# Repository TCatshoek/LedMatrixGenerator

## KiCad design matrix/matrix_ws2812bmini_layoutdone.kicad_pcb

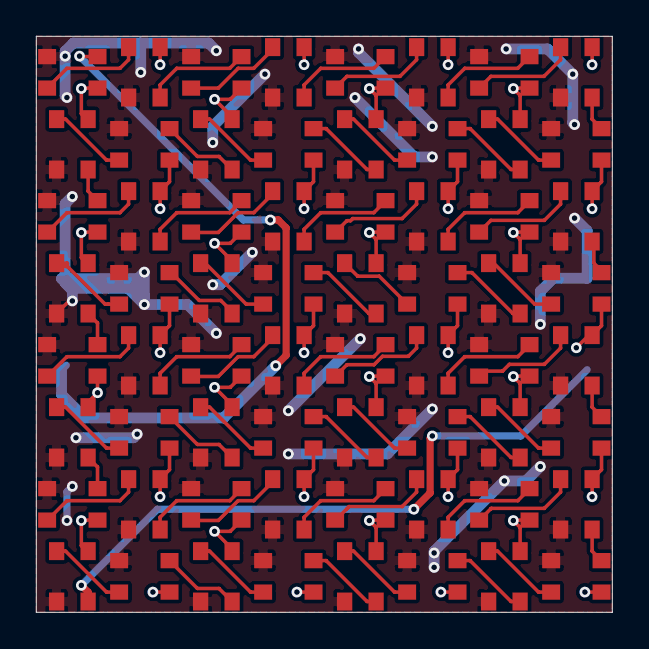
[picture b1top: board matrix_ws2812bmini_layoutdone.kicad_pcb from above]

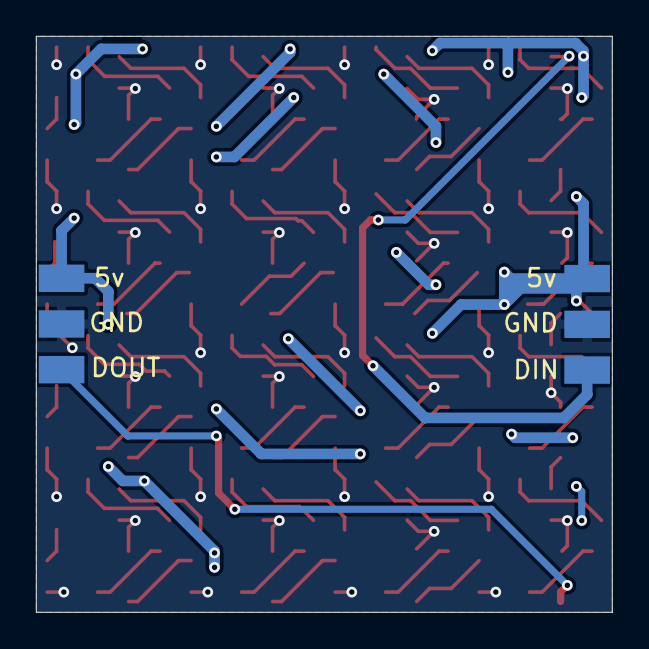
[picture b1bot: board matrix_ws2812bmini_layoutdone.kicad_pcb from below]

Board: 2 copper layers, 32.0 x 32.0 mm, 66 parts (2 on the bottom side), 67 nets.

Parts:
D1, D2, D3, D4, D5, D6, D7, D8, D9, D10, D11, D12, D13, D14, D15, D16, D17, D18, D19, D20, D21, D22, D23, D24, D25, D26, D27, D28, D29, D30, D31, D32, D33, D34, D35, D36, D37, D38, D39, D40, D41, D42, D43, D44, D45, D46, D47, D48, D49, D50, D51, D52, D53, D54, D55, D56, D57, D58, D59, D60, D61, D62, D63, D64: WS2812B-MINI; LED_SK6812MINI_PLCC4_3.5x3.5mm_P1.75mm_lowprofile
J1: Conn_01x03; smd_pads_3_in
J2: Conn_01x03; smd_pads_3_out

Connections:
GND: D1.3, D2.3, D3.3, D4.3, D5.3, D6.3, D7.3, D8.3, D9.3, D10.3, D11.3, D12.3, D13.3, D14.3, D15.3, D16.3, D17.3, D18.3, D19.3, D20.3, D21.3, D22.3, D23.3, D24.3, D25.3, D26.3, D27.3, D28.3, D29.3, D30.3, D31.3, D32.3, D33.3, D34.3, D35.3, D36.3, D37.3, D38.3, D39.3, D40.3, D41.3, D42.3, D43.3, D44.3, D45.3, D46.3, D47.3, D48.3, D49.3, D50.3, D51.3, D52.3, D53.3, D54.3, D55.3, D56.3, D57.3, D58.3, D59.3, D60.3, D61.3, D62.3, D63.3, D64.3, J1.2, J2.2
unnamed: D1.2, D2.4
unnamed: D2.2, D3.4
unnamed: D3.2, D4.4
unnamed: D4.2, D5.4
unnamed: D5.2, D6.4
unnamed: D6.2, D7.4
unnamed: D7.2, D8.4
unnamed: D8.2, D9.4
unnamed: D9.2, D10.4
unnamed: D10.2, D11.4
unnamed: D11.2, D12.4
unnamed: D12.2, D13.4
unnamed: D13.2, D14.4
unnamed: D14.2, D15.4
unnamed: D15.2, D16.4
unnamed: D16.2, D17.4
unnamed: D17.2, D18.4
unnamed: D18.2, D19.4
unnamed: D19.2, D20.4
unnamed: D20.2, D21.4
unnamed: D21.2, D22.4
unnamed: D22.2, D23.4
unnamed: D23.2, D24.4
unnamed: D24.2, D25.4
unnamed: D25.2, D26.4
unnamed: D26.2, D27.4
unnamed: D27.2, D28.4
unnamed: D28.2, D29.4
unnamed: D29.2, D30.4
unnamed: D30.2, D31.4
unnamed: D31.2, D32.4
unnamed: D32.2, D33.4
unnamed: D33.2, D34.4
unnamed: D34.2, D35.4
unnamed: D35.2, D36.4
unnamed: D36.2, D37.4
unnamed: D37.2, D38.4
unnamed: D38.2, D39.4
unnamed: D39.2, D40.4
unnamed: D40.2, D41.4
unnamed: D41.2, D42.4
unnamed: D42.2, D43.4
unnamed: D43.2, D44.4
unnamed: D44.2, D45.4
unnamed: D45.2, D46.4
unnamed: D46.2, D47.4
unnamed: D47.2, D48.4
unnamed: D48.2, D49.4
unnamed: D49.2, D50.4
unnamed: D50.2, D51.4
unnamed: D51.2, D52.4
unnamed: D52.2, D53.4
unnamed: D53.2, D54.4
unnamed: D54.2, D55.4
unnamed: D55.2, D56.4
unnamed: D56.2, D57.4
unnamed: D57.2, D58.4
unnamed: D58.2, D59.4
unnamed: D59.2, D60.4
unnamed: D60.2, D61.4
unnamed: D61.2, D62.4
unnamed: D62.2, D63.4
unnamed: D63.2, D64.4
unnamed: D1.4, J1.3
unnamed: D64.2, J2.3
VCC: D1.1, D2.1, D3.1, D4.1, D5.1, D6.1, D7.1, D8.1, D9.1, D10.1, D11.1, D12.1, D13.1, D14.1, D15.1, D16.1, D17.1, D18.1, D19.1, D20.1, D21.1, D22.1, D23.1, D24.1, D25.1, D26.1, D27.1, D28.1, D29.1, D30.1, D31.1, D32.1, D33.1, D34.1, D35.1, D36.1, D37.1, D38.1, D39.1, D40.1, D41.1, D42.1, D43.1, D44.1, D45.1, D46.1, D47.1, D48.1, D49.1, D50.1, D51.1, D52.1, D53.1, D54.1, D55.1, D56.1, D57.1, D58.1, D59.1, D60.1, D61.1, D62.1, D63.1, D64.1, J1.1, J2.1

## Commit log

2021-04-06 8x8 matrix done
